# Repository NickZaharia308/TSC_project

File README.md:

# Nicusor-Alexandru Zaharia 335CA – Open-Source E-Book Reader

## Description
**OpenBook** is a fully open-source, ESP32-C6-powered e-book reader designed to be affordable, customizable, and easy to manufacture. It features a crisp e-paper display, modular hardware, and full documentation – empowering developers and hardware enthusiasts to build their own e-reader from scratch.

The project contains the **Product Design** with a complete [`schematic`](Hardware/Schematic.sch), [`PCB`](Hardware/PCB_2D.brd) and [`3D Model`](Mechanical/Completed%203D%20model%20v1.f3z).

---

## Repository Hierarchy

- Hardware
  ├── Schematic file (.sch)  
  └── Board layout file (.brd)  

- Manufacturing
  ├── Gerber files archive (gerbers.zip)  
  ├── Bill of Materials file (.bom)  
  └── Pick and Place file (.cpl)  

- Mechanical
  ├── 3D model of the complete device (PCB + battery + display + case) – exploded view (.step)  
  └── Fusion 360 project file of the complete device  

- Images
  └── Renders of the device

- LICENSE  
- README.md  

---

##  E-Book Reader Block Diagram

---

##   Design Process

1.  **Schematic Design:** The schematic was meticulously designed to align with the project's specified requirements. It highlights the important `components and modules`.
    
2.  **PCB Redesign:** The PCB layout was generated based on the size of the enclosure, and `components were strategically placed` according to design guidelines and best practices.
    
3.  **Routing Implementation:** Routing was used on both the top and bottom layers of the PCB. `Signal traces` were set to a width of 0.15mm while `the power traces` were organized into a dedicated net class named `Power class` routed with a width of 0.3mm to ensure optimal power distribution.
    
4.  **Ground Plane and Via Stitching:** `Ground planes` were implemented on both the top and bottom layers. `Via stitching` was applied, particularly in proximity to the ESP module, to establish effective interlayer connections and minimize ground impedance. `Vias` were used to interconnect the ground planes.
    
5.  **3D Model Integration:** `3D models` of the components were found with the link to them at the bottom of the README, integrated into Fusion 360, and accurately placed on the `PCB layout` to facilitate mechanical design and visualization.
    
6.  **Enclosure Integration:** The PCB was integrated into its intended enclosure. The enclosure design was adapted to accommodate buttons, connectors, and other external interface elements. `Battery` and `display` 3D models were developed positioned within the enclosure to ensure proper fit and alignment.

7.  **Export and Manufacturing Preparation:** The final stage involved `generating all necessary manufacturing` documentation, including Gerber files, Pick and Place (CPL) data, and the Bill of Materials (BOM), to prepare the design for fabrication and assembly.

---

## Decision Making

I switched the original [battery](https://www.tme.eu/Document/e0683d8c34e6d878124489f71bffb6ee/cel0014.pdf) from cellevia batteries with a similar [one](https://www.elektronik.ropla.eu/pdf/stock/aky/aky0099.pdf) (same electrical parameters) from akyga with a size that enters well in the enclosure and beside that it also has a lifecycle of `500 charges` as opossed to only `300 charges`

---

## Component Description and Interaction

### Microcontroller

* **ESP32-C6-WROOM-1-NI (U2):** This is the core of the board, a powerful microcontroller with Wi-Fi and Bluetooth Low Energy (BLE) connectivity. It is responsible for controlling all other components, processing data, and external communication.

### Power Supply

* **Li-Po Battery Charging Controller (MCP73831):** This circuit enables the board to be powered from a Li-Po battery and manages the charging process when an external power source is connected via the USB-C connector.
* **USB C connector:** Provides the interface for powering the board and potentially for data transfer. Includes `ESD (Electrostatic Discharge) protection`.
* **LDO Voltage Regulator (XC8220A331MR-G):** An LDO (Low Dropout) voltage regulator is used to provide a `stable 3.3V voltage` required for powering most of the components on the board, derived from the battery voltage or USB.
* **Supercapacitor (CPH3225A):** A supercapacitor is present, possibly to provide a backup power source for certain critical functions, such as the RTC module, in case the main power supply is interrupted.
* **Reverse Polarity Protection (MBR0530):** Schottky diodes are used to protect the circuits against incorrect polarity connection of the power source.
* **Capacitors (electrolytic, tantalum, ceramic):** Various types and values of capacitors are used for `power supply filtering, decoupling, and temporary energy storage` at different points in the circuit.

### Display

* **E-Paper Display Header (FH34SR-24S-0.5SH):** A header connector is provided for connecting an `E-Paper display`. This type of display is known for its low power consumption and image retention without power.
* **Display Type Selector:** A set of pull-up/pull-down resistors connected to ESP32-C6 pins allows for the detection of the connected E-Paper display type.

### Sensors

* **Environmental Sensor BME688:** This sensor integrates `temperature, humidity, atmospheric pressure, and air quality` (VOC - volatile organic compounds) measurement functions. It communicates with the ESP32-C6 via the `I2C` interface.
* **RTC Module DS3231SN:** A Real-Time Clock (RTC) module that maintains accurate time and date information, even when the board is powered off, being powered by the supercapacitor or a small battery. It communicates with the ESP32-C6 via `the I2C interface`.
* **Battery Charge Level (MAX17048G+T10):** A dedicated integrated circuit for monitoring the charge level of the Li-Po battery. It communicates with the ESP32-C6 via the `I2C interface`.

### User Interaction

* **Boot/IO Button (BOOT BUTTON):** A button used to force the ESP32-C6 into bootloader mode for programming or to perform an application-specific function.
* **Reset Button (RESET BUTTON):** A button to reset the ESP32-C6 microcontroller.
* **Change Button (CHANGE):** A button with an application-defined functionality, for navigation or selection.
* **CHG LED:** An LED indicator for the battery charging status.

### External Memory

* **External NOR Flash 64MB (W25Q512JVEIQ):** An external `64MB SPI flash memory`, used for storing firmware, data, or additional resources required by the application, exceeding the ESP32-C6's internal flash memory capacity. Good to keep `more books to read`.

### Connectivity and Interfaces

* **USB C connector:** For power and potential data transfer.
* **E-Paper Display Header:** Dedicated connector for the E-Paper display.
* **Qwiic/Stemma QT Connector:** A standard `I2C connector that allows for easy connection of additional I2C-compatible sensors or actuators`.
* **SPI ESD Protection Lines:** ESD protection circuits for the SPI communication lines, used for the external flash memory interface.
* **Test Pads (TP1-TP17):** Test points distributed across the board to facilitate debugging and `signal verification`.

### Miscellaneous

* **GND:** Multiple ground points for ensuring a stable voltage reference.
* **Resistors:** Various resistors are used for `pull-up, pull-down, current limiting, and voltage division`.
* **Diodes:** Diodes with various purposes, such as `protection or rectification`.
* **Inductor:** An inductor, part of the `power supply circuit or for EMI filtering`.
* **MOSFETs:** MOSFET transistors used for power switching or other control functions.

##   ESP32-C6 Pin Usage

The following list details the ESP32-C6 pins used and the reason for their use:

* **Pin 10 (3V3):** Power supply pin for the ESP32-C6, connected to the 3.3V rail generated by the LDO.
* **Pin 8 (GHD):** A ground (GND) pin.
* **Pin 5 (GHD):** A ground (GND) pin.
* **Pin 20 (EN):** Enable pin for the ESP32-C6, controlled by a power management circuit or connected to a pull-up to keep it active.
* **Pin 21 (1011):** Connected to the BOOT button. It is configured as an input and used to initiate the ESP32-C6's bootloader mode at startup or reset. A pull-up resistor (R BOOT 10K) ensures a default high logic level, and pressing the button connects it to GND.
* **Pin 22 (1013):** Connected to the RESET button. Similar to the BOOT button, it's an input used to reset the microcontroller.
* **Pin 23 (1013):** Connected to the CHANGE button. It is configured as an input and used to detect user action. A pull-up resistor (10K) ensures a default high logic level, and pressing the button connects it to GND.
* **Pin 19 (102):** Connected to the SDA (Serial Data) line of the I2C bus. This line is used for bidirectional data communication with the BME688 sensor, the DS3231SN RTC module, and the MAX17048G battery monitoring circuit. Pull-up resistors will be present on the I2C bus.
* **Pin 18 (1015):** Connected to the SCL (Serial Clock) line of the I2C bus. This line provides the synchronization clock signal for I2C communication with the peripherals mentioned above. Similar to SDA, it requires pull-up resistors.
* **Pin 17 (132):** Connected to the CE (Chip Enable) pin of the external flash memory W25Q512JVEIQ. This pin is used to select the flash memory chip for SPI communication.
* **Pin 16 (10220):** Connected to the HOLD/RESET pin of the external flash memory. This pin has multiple functions related to controlling the write and read operations of the flash memory.
* **Pin 15 (10):** Connected to the WP (Write Protect) pin of the external flash memory. This pin is used to protect certain sectors of the flash memory against accidental writing.
* **Pin 14 (CE BAT):** Connected to the CE (Chip Enable) pin of the MAX17048G battery monitoring circuit. Used to enable communication with this circuit on the I2C bus.

**Pins Connected to E-Paper Display Header (FH34SR-24S-0.5SH):**

Several ESP32-C6 pins will be connected to the E-Paper display header to control and transmit data to it.

* Powering the display (via "EPD Power").
* Transmitting the data and control signals necessary for updating the image on the display. This could include pins for an SPI interface (data, clock, chip select) or another interface specific to the E-Paper display controller.

**Pins Connected to BME688 Sensor:**

* **SDA (connected to Pin 19 of ESP32-C6):** I2C data line.
* **SCL (connected to Pin 18 of ESP32-C6):** I2C clock line.
* **VDDIO:** Power supply pin for the sensor's logic interface, connected to 3.3V.
* **VDD:** Power supply pin for the sensor, connected to 3.3V.
* **CSH:** Chip Select pin for the SPI interface.
* **SCK:** Serial Clock pin for the SPI interface.
* **SDO:** Serial Data Out pin for the SPI interface.

**Pins Connected to DS3231SN RTC Module:**

* **SDA (connected to Pin 19 of ESP32-C6):** I2C data line.
* **SCL (connected to Pin 18 of ESP32-C6):** I2C clock line.
* **VCC:** Power supply pin, connected to 3.3V or the supercapacitor voltage to maintain RTC operation.
* **SQW/INT# (ALERT):** An output pin that can be configured as a square wave output or an alarm/interrupt output, connected to a GPIO pin of the ESP32-C6.

**Pins Connected to MAX17048G Battery Charge Level Circuit:**

* **SDA (connected to Pin 19 of ESP32-C6):** I2C data line.
* **SCL (connected to Pin 18 of ESP32-C6):** I2C clock line.
* **CE (connected to Pin 14 of ESP32-C6):** Chip Enable pin for selecting the I2C circuit.
* **ALERT:** An alert output pin that can indicate low battery level or other events, connected to a GPIO pin of the ESP32-C6.

**Pins Connected to W25Q512JVEIQ (U1) External Flash Memory:**

* **CS# (Chip Select):** Connected to Pin 17 of ESP32-C6.
* **CLK (Serial Clock):** An ESP32-C6 SPI CLK pin.
* **MOSI (Master Out Slave In):** An ESP32-C6 SPI MOSI pin.
* **MISO (Master In Slave Out):** An ESP32-C6 SPI MISO pin.
* **HOLD/RESET#:** Connected to Pin 16 of ESP32-C6.
* **WP# (Write Protect):** Connected to Pin 15 of ESP32-C6.

**Pins Connected to Qwiic/Stemma QT Connector:**

* **SDA:** Connected to Pin 19 of ESP32-C6.
* **SCL:** Connected to Pin 18 of ESP32-C6.
* **VCC (3V3):** Power supply for connected devices.
* **GND:** Ground.

---

## Images

---

## Bill of Materials

| Component                                        | Product Link                | Datasheet                        |
|--------------------------------------------------|-----------------------------------|-----------------------------------|
| ESP32-C6 WROOM-1-N8                              | [SnapMagic](https://www.snapeda.com/parts/ESP32-C6-WROOM-1-N8/Espressif+Systems/view-part/?ref=eda)         | [Datasheet](https://www.snapeda.com/parts/ESP32-C6-WROOM-1-N8/Espressif%20Systems/datasheet/)     |
| ESP32C6 Varistor 1812                            | [Mouser](https://ro.mouser.com/ProductDetail/EPCOS-TDK/B72520T0350K062?qs=dEfas%2FXlABIszF52uu7vrg%3D%3D)        | [Datasheet](https://www.tdk-electronics.tdk.com/inf/75/db/CTVS_14/Surge_protection_series.pdf)     |
| ESP32 WROVER 0805 Capacitor                      | [Mouser](https://ro.mouser.com/ProductDetail/KYOCERA-AVX/SD0805S020S1R0?qs=jCA%252BPfw4LHbpkAoSnwrdjw%3D%3D)         | [Datasheet](https://ro.mouser.com/datasheet/2/40/schottky-3165252.pdf)     |
| ESP32 WROVER BME680 Sensor                       | [SnapMagic](https://www.snapeda.com/parts/BME680/Bosch/view-part/?welcome=home)        | [Datasheet](https://www.snapeda.com/parts/BME680/Bosch%20Sensortec/datasheet/)     |
| ESP32 WROVER MCP73831 Power Management           | [Mouser](https://eu.mouser.com/ProductDetail/Microchip-Technology/MCP73831T-2ACI-OT?qs=yUQqVecv4qvbBQBGbHx0Mw%3D%3D)         | [Datasheet](https://eu.mouser.com/datasheet/2/268/MCP73831_Family_Data_Sheet_DS20001984H-3441711.pdf)     || ESP32 WROVER P-Channel MOSFET                    | [Component Search Engine](https://componentsearchengine.com/part-view/DMG2305UX-7/Diodes%20Incorporated)         | [Datasheet](https://www.diodes.com//assets/Datasheets/DMG2305UX.pdf)     |
| LED Chip 0603                                    | [SnapMagic](https://www.snapeda.com/parts/KP-1608SURCK/Kingbright/view-part/?ref=search&t=LED%200603)        | [Datasheet](https://www.snapeda.com/parts/KP-1608SURCK/Kingbright/datasheet/)     |
| SJ                                               | [GrabCad](https://grabcad.com/library/solder-jumpers-1)         | [Datasheet](https://en.wikipedia.org/wiki/HTTP_404)     |
| LTSPICE Resistor 0402                            | [Component Search Engine](https://componentsearchengine.com/part-view/R0402%201%25%20100%20K%20(RC0402FR-07100KL)/YAGEO)        | [Datasheet](https://www.yageo.com/upload/media/product/products/datasheet/rchip/PYu-RC_Group_51_RoHS_L_12.pdf)     |
| RCL CPOL 3528                                    | [SnapMagic](https://www.snapeda.com/parts/TAJB475K025RNJ/AVX/view-part/?ref=dk&t=capacitor%203528&con_ref=None)        | [Datasheet](https://s3.amazonaws.com/snapeda/datasheet/TAJB475K025RNJ_AVX.pdf)     |
| 112A-TAAR-R03                                    | [Comet](https://store.comet.srl.ro/Catalogue/Product/43497/)         | [Datasheet](https://store.comet.bg/download-file.php?id=27596)     |
| Capacitor 0402                                   | [Component Search Engine](https://componentsearchengine.com/part-view/CC0402MRX5R5BB106/YAGEO)         | [Datasheet](https://componentsearchengine.com/Datasheets/2/CC0402MRX5R5BB106.pdf)     |
| 744043680 IND                                    | [Mouser](https://eu.mouser.com/ProductDetail/Wurth-Elektronik/744043680?qs=PGXP4M47uW6VkZq%252BkzjrHA%3D%3D)        | [Datasheet](https://www.we-online.com/components/products/datasheet/744043680.pdf)     |
| BD5229G-TR                                       | [Component Search Engine](https://componentsearchengine.com/part-view/BD5229G-TR/ROHM%20Semiconductor)         | [Datasheet](https://datasheet.datasheetarchive.com/originals/distributors/Datasheets_SAMA/f2b9741ef86007909f138d561a359946.pdf)     |
| Custom Button                                    | [Panasonic](https://industry.panasonic.com/global/en/products/control/switch/light-touch/number/evqpuj02k)        | [Datasheet](https://industry.panasonic.com/global/en/downloads?tab=catalog&small_g_cd=203&part_no=EVQPUJ02K&q=RVZRUFVKMDJLJTdDMTMlN0MyMDMlN0MzNDU5JTdDMSU3QyU3QzIlN0M%3D)     |
| CPH3225A                                         | [SnapMagic](https://www.snapeda.com/parts/CPH3225A/Seiko+Instruments/view-part/?ref=eda)         | [Datasheet](https://www.snapeda.com/parts/CPH3225A/Seiko%20Instruments/datasheet/)     |
| DS3231SN RTC                                     | [SnapMagic](https://www.snapeda.com/parts/DS3231SN%23/Analog+Devices/view-part/?ref=eda)        | [Datasheet](https://www.snapeda.com/parts/DS3231SN%23/Analog%20Devices/datasheet/)     |
| FH34SRJ-24S-0.5SH Connector                      | [Component Search Engine](https://componentsearchengine.com/part-view/FH34SRJ-24S-0.5SH(99)/Hirose)        | [Datasheet](https://www.hirose.com/en/product/document?clcode=CL0580-1255-6-99&productname=FH34SRJ-24S-0.5SH(99)&series=FH34SRJ&documenttype=2DDrawing&lang=en&documentid=0000990903)     |
| MAX17048G+T10 Battery Fuel Gauge                 | [SnapMagic](https://www.snapeda.com/parts/MAX17048G+T10/Analog+Devices/view-part/?ref=eda)         | [Datasheet](https://www.snapeda.com/parts/MAX17048G+T10/Analog%20Devices/datasheet/)     |
| MBR0530 Schottky Diode                           | [SnapMagic](https://www.snapeda.com/parts/MBR0530/Onsemi/view-part/?ref=eda)        | [Datasheet](https://www.snapeda.com/parts/MBR0530/ON%20Semiconductor/datasheet/)     |
| PGB1010603MR Inductor                            | [SnapMagic](https://www.snapeda.com/parts/PGB1010603MR/Littelfuse/view-part/?ref=eda)         | [Datasheet](https://www.snapeda.com/parts/PGB1010603MR/Littelfuse%20Inc./datasheet/)     |
| QWIIC Connector                                  | [Mouser](https://eu.mouser.com/ProductDetail/Adafruit/4208?qs=PzGy0jfpSMtbScLbr0L5dw%3D%3D)        | [Datasheet](https://en.wikipedia.org/wiki/HTTP_404)     |
| USB4110-GF-A USB Hub                             | [Component Search Engine](https://componentsearchengine.com/part-view/USB4110-GF-A/GCT%20(GLOBAL%20CONNECTOR%20TECHNOLOGY))         | [Datasheet](https://gct.co/files/drawings/usb4110.pdf)     |
| SI1308EDL-T1-GE3 MOSFET                          | [SnapMagic](https://www.snapeda.com/parts/SI1308EDL-T1-GE3/Vishay+Siliconix/view-part/?ref=eda)        | [Datasheet](https://en.wikipedia.org/wiki/HTTP_404)     |
| TPTP20R                                          | [Comet](https://easyeda.com/component/7524403feb2642ac9f9f26dfb93ceacf)         | [Datasheet](https://easyeda.com/component/7524403feb2642ac9f9f26dfb93ceacf)     |
| USBLC6-2SC6Y USB Surge Protection                | [SnapMagic](https://www.snapeda.com/parts/USBLC6-2SC6Y/STMicroelectronics/view-part/?ref=eda)        | [Datasheet](https://www.snapeda.com/parts/USBLC6-2SC6Y/STMicroelectronics/datasheet/)     |
| W25Q512JVEIQ Flash Memory                        | [SnapMagic](https://www.snapeda.com/parts/W25Q512JVEIQ/Winbond+Electronics/view-part/?ref=eda)         | [Datasheet](https://www.snapeda.com/parts/W25Q512JVEIQ/Winbond%20Electronics/datasheet/)     |
| XC6220A331MR-G Voltage Regulator                 | [Component Search Engine](https://componentsearchengine.com/part-view/XC6220A331MR-G/Torex)        | [Datasheet](https://product.torexsemi.com/system/files/series/xc6220.pdf)     |

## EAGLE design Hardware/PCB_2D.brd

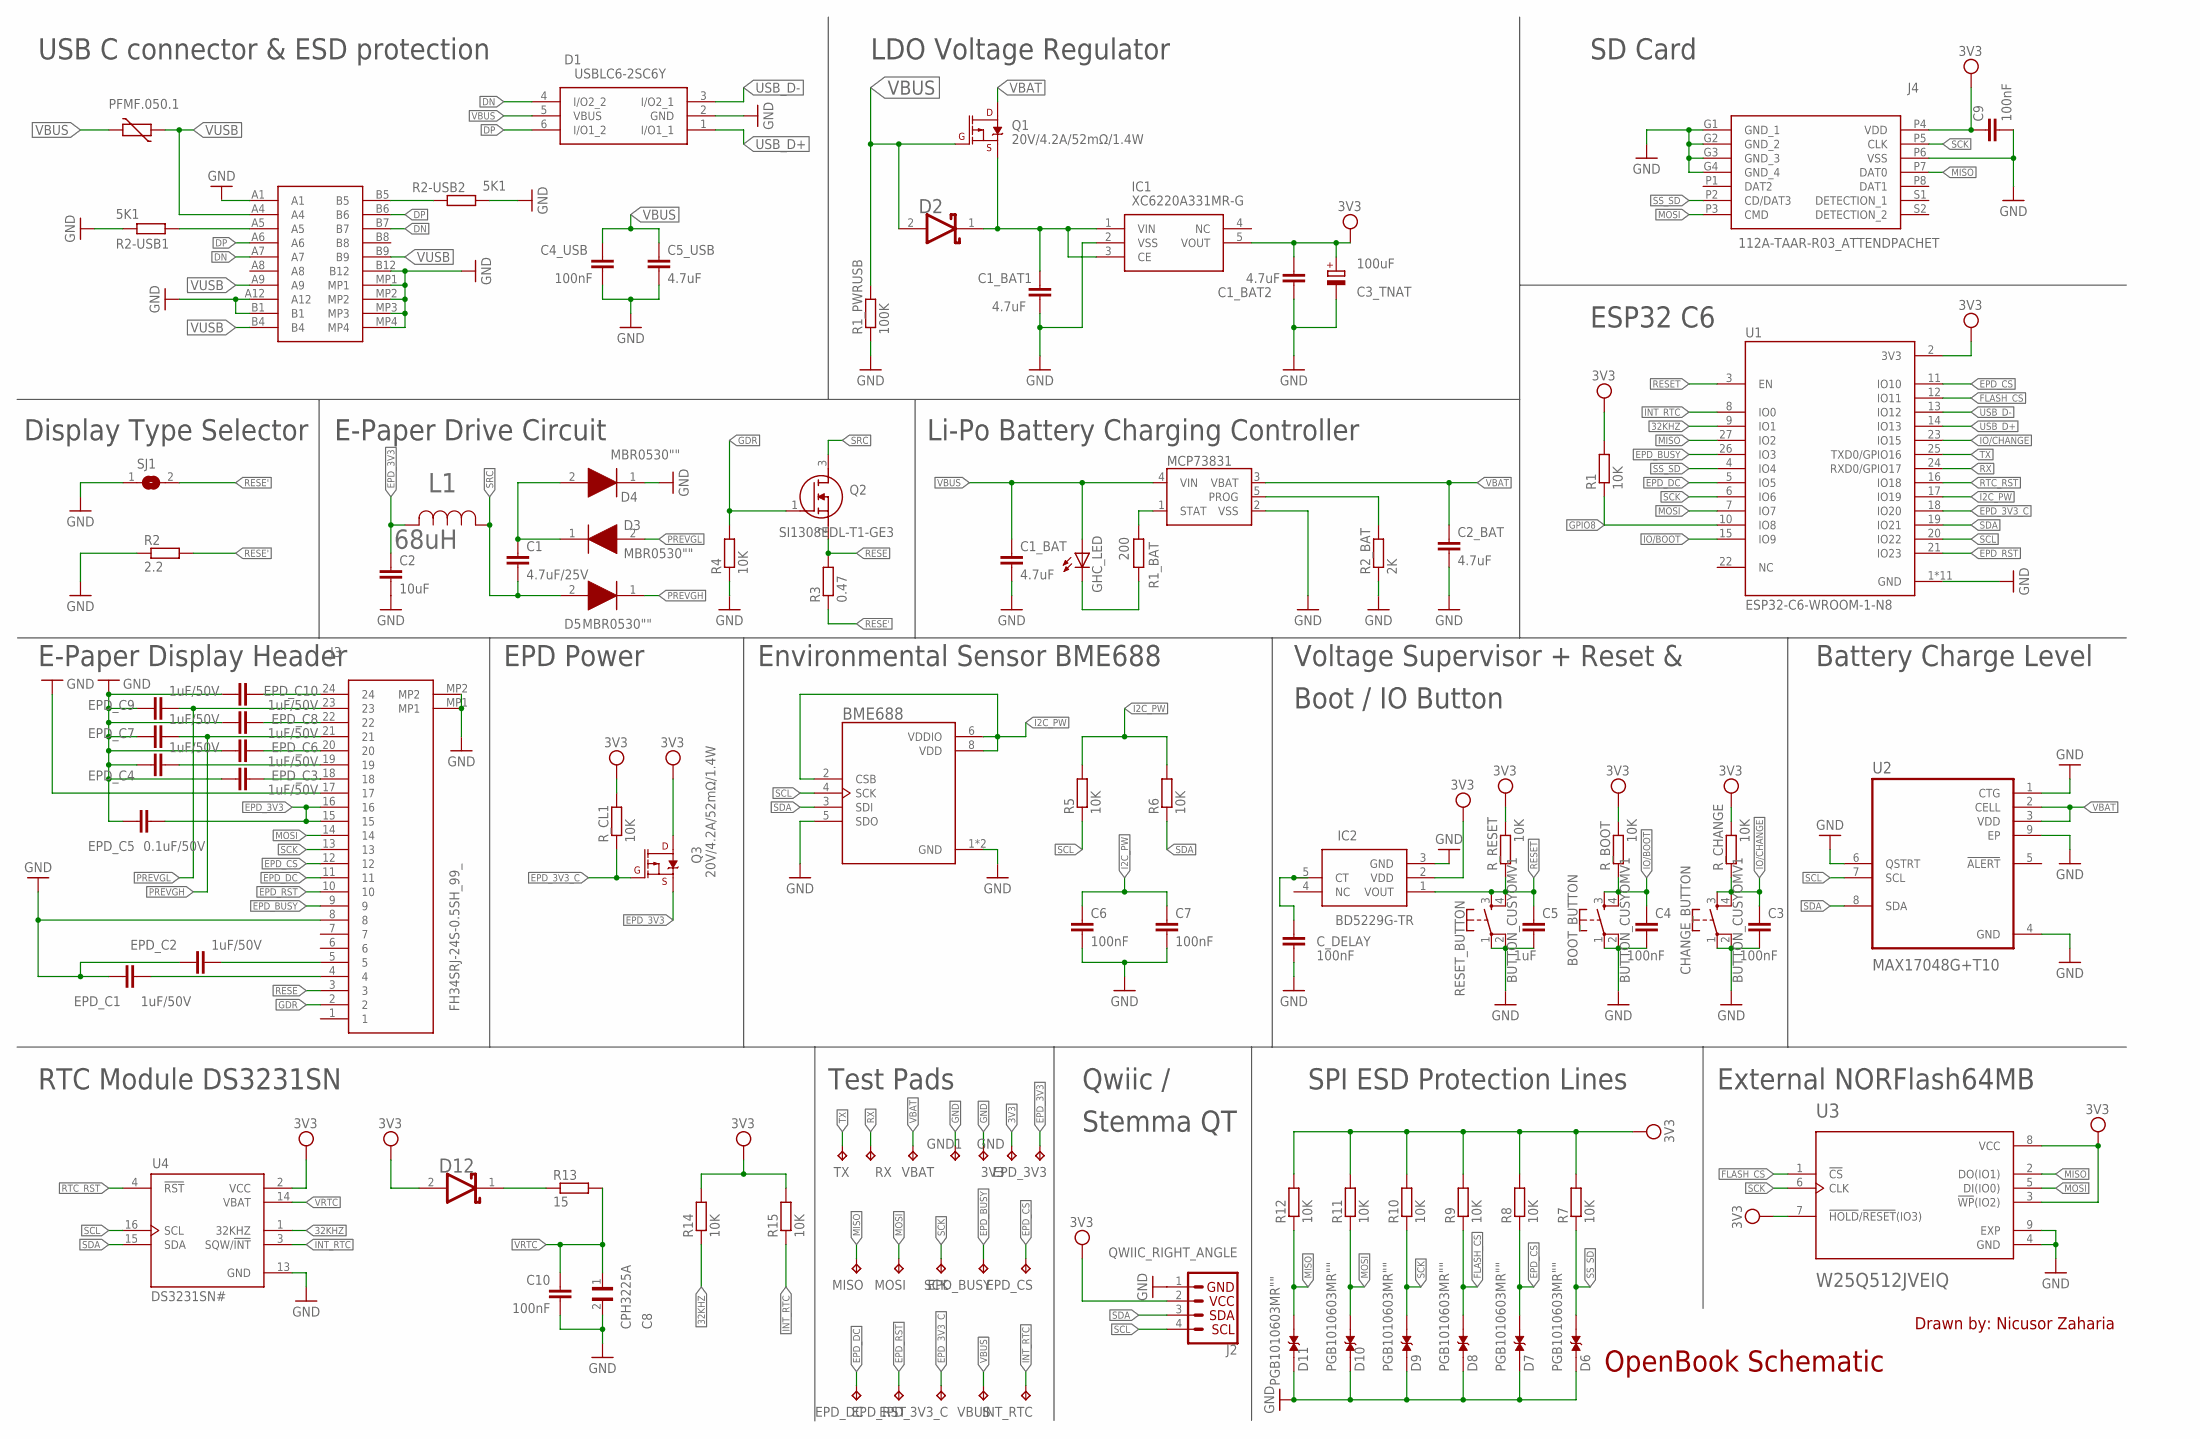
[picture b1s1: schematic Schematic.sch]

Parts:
3V3: TPTP20R; TP20R
BME688: ESP32_WROVER_BME680_BME680; ESP32_WROVER_BME680_PSON80P300X300X100-8N
BOOT_BUTTON: BUTTON_CUSYOMV1; MYBUTTON
C1: 4.7uF/25V; EAGLE-LTSPICE_C0402
C1_BAT, C1_BAT1, C1_BAT2, C2_BAT, C5_USB: 4.7uF; EAGLE-LTSPICE_C0402
C2: 10uF; EAGLE-LTSPICE_C0402
C3, C4, C4_USB, C6, C7, C9, C10: 100nF; EAGLE-LTSPICE_C0402
C3_TNAT: 100uF; RCL_CT3528
C5: 1uF; EAGLE-LTSPICE_C0402
C8: CPH3225A; CAPCP3225X100N
CHANGE_BUTTON: BUTTON_CUSYOMV1; MYBUTTON
C_DELAY: 100nF; EAGLE-LTSPICE_C0402
D1: USBLC6-2SC6Y; SOT95P280X145-6N
D2, D12: ESP32_WROVER_AVX---SD0805S020S1R0_AVX_SD0805S020S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; ESP32_WROVER_AVX---SD0805S020S1R0_AVX_SD0805S020S1R0_0
D3, D4, D5: MBR0530""; SOD3716X135N
D6, D7, D8, D9, D10, D11: PGB1010603MR""; DIOC1608X36N
EPD_3V3, EPD_3V3_C: TPTP20R; TP20R
EPD_BUSY: TPTP20R; TP20R
EPD_C1, EPD_C2, EPD_C3, EPD_C4, EPD_C6, EPD_C7, EPD_C8, EPD_C9, EPD_C10: 1uF/50V; EAGLE-LTSPICE_C0402
EPD_C5: 0.1uF/50V; EAGLE-LTSPICE_C0402
EPD_CS: TPTP20R; TP20R
EPD_DC: TPTP20R; TP20R
EPD_RST: TPTP20R; TP20R
GHC_LED: ADAFRUIT_LEDCHIP-LED0603; ADAFRUIT_CHIP-LED0603
GND, GND1: TPTP20R; TP20R
IC1: XC6220A331MR-G; SOT95P280X120-5N
IC2: BD5229G-TR; SOT95P280X125-5N
INT_RTC: TPTP20R; TP20R
J1: SAMACSYS_PARTS_USB4110-GF-A; SAMACSYS_PARTS_USB4110GFA
J2: QWIIC_RIGHT_ANGLE; JST04_1MM_RA
J3: FH34SRJ-24S-0.5SH_99_; FH34SRJ24S05SH99
J4: 112A-TAAR-R03_ATTENDPACHET; 112ATAARR03ATTEND
L1: 68uH; IND_4828-WE-TPC_WRE
MCP73831: ESP32_WROVER_SPARKFUN-IC-POWER_MCP73831; ESP32_WROVER_SPARKFUN-IC-POWER_SOT23-5
MISO: TPTP20R; TP20R
MOSI: TPTP20R; TP20R
PFMF.050.1: ESP32C6_VARISTORCN1812; ESP32C6_VARISTOR_CT/CN1812
Q1, Q3: 20V/4.2A/52mΩ/1.4W; ESP32_WROVER_SPARKFUN-DISCRETESEMI_SOT23-3
Q2: SI1308EDL-T1-GE3; SOT65P210X110-3N
R1, R4, R5, R6, R7, R8, R9, R10, R11, R12, R14, R15: 10K; ESP32_WROVER_EAGLE-LTSPICE_R0402
R1_BAT: 200; ESP32_WROVER_EAGLE-LTSPICE_R0402
R1_PWRUSB: 100K; ESP32_WROVER_EAGLE-LTSPICE_R0402
R2: 2.2; ESP32_WROVER_EAGLE-LTSPICE_R0402
R2-USB1, R2-USB2: 5K1; ESP32_WROVER_EAGLE-LTSPICE_R0402
R2_BAT: 2K; ESP32_WROVER_EAGLE-LTSPICE_R0402
R3: 0.47; ESP32_WROVER_EAGLE-LTSPICE_R0402
R13: 15; ESP32_WROVER_EAGLE-LTSPICE_R0402
RESET_BUTTON: BUTTON_CUSYOMV1; MYBUTTON
RX: TPTP20R; TP20R
R_BOOT: 10K; ESP32_WROVER_EAGLE-LTSPICE_R0402
R_CHANGE: 10K; ESP32_WROVER_EAGLE-LTSPICE_R0402
R_CL1: 10K; ESP32_WROVER_EAGLE-LTSPICE_R0402
R_RESET: 10K; ESP32_WROVER_EAGLE-LTSPICE_R0402
SCK: TPTP20R; TP20R
SJ1: SJ
TX: TPTP20R; TP20R
U1: ESP32-C6-WROOM-1-N8; XCVR_ESP32-C6-WROOM-1-N8
U2: MAX17048G+T10; SON50P200X200X80-9N
U3: W25Q512JVEIQ; SON127P600X800X80-9N
U4: DS3231SN#; SOIC127P1032X265-16N
VBAT: TPTP20R; TP20R
VBUS: TPTP20R; TP20R

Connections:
3V3: 3V3.TP, C1_BAT2.1, C3_TNAT.+, C9.1, D12.2 (ANODE), IC1.5 (VOUT), IC2.2 (VDD), J2.2, J4.P4 (VDD), Q3.3 (D), R1.2, R7.2, R8.2, R9.2, R10.2, R11.2, R12.2, R14.2, R15.2, R_BOOT.2, R_CHANGE.2, R_CL1.2, R_RESET.2, U1.2 (3V3), U3.3 (!WP!(IO2)), U3.7 (!HOLD!/!RESET!(IO3)), U3.8 (VCC), U4.2 (VCC)
32KHZ: R14.1, U1.9 (IO1), U4.1 (32KHZ)
DN: D1.4 (I/O2_2), J1.A7, J1.B7
DP: D1.6 (I/O1_2), J1.A6, J1.B6
EPD_3V3: C2.1, EPD_3V3.TP, EPD_C5.2, J3.15, J3.16, L1.2, Q3.2 (S)
EPD_3V3_C: EPD_3V3_C.TP, Q3.1 (G), R_CL1.1, U1.18 (IO20)
EPD_BUSY: EPD_BUSY.TP, J3.9, U1.26 (IO3)
EPD_CS: D7.2, EPD_CS.TP, J3.12, R8.1, U1.11 (IO10)
EPD_DC: EPD_DC.TP, J3.11, U1.5 (IO5)
EPD_RST: EPD_RST.TP, J3.10, U1.21 (IO23)
FLASH_CS: D8.2, R9.1, U1.12 (IO11), U3.1 (!CS)
GDR: J3.2, Q2.1 (G), R4.2
GND: BME688.1 (GND), BME688.5 (SDO), BME688.7 (GND), BOOT_BUTTON.1, BOOT_BUTTON.2, C1_BAT.2, C1_BAT1.2, C1_BAT2.2, C2.2, C2_BAT.2, C3.2, C3_TNAT.-, C4.2, C4_USB.2, C5.2, C5_USB.2, C6.2, C7.2, C8.2, C9.2, C10.2, CHANGE_BUTTON.1, CHANGE_BUTTON.2, C_DELAY.2, D1.2 (GND), D4.1 (K), D6.1, D7.1, D8.1, D9.1, D10.1, D11.1, EPD_C1.1, EPD_C2.1, EPD_C3.1, EPD_C4.1, EPD_C5.1, EPD_C6.1, EPD_C7.1, EPD_C8.1, EPD_C9.1, EPD_C10.1, GND.TP, GND1.TP, IC1.2 (VSS), IC2.3 (GND), J1.A1, J1.A12, J1.B1, J1.B12, J1.MP1, J1.MP2, J1.MP3, J1.MP4, J2.1, J3.8, J3.17, J3.MP1, J3.MP2, J4.G1 (GND_1), J4.G2 (GND_2), J4.G3 (GND_3), J4.G4 (GND_4), J4.P6 (VSS), MCP73831.2 (VSS), R1_PWRUSB.1, R2.1, R2-USB1.1, R2-USB2.2, R2_BAT.1, R4.1, RESET_BUTTON.1, RESET_BUTTON.2, SJ1.1, U1.1 (GND), U1.28 (GND), U1.29_1 (GND), U1.29_2 (GND), U1.29_3 (GND), U1.29_4 (GND), U1.29_5 (GND), U1.29_6 (GND), U1.29_7 (GND), U1.29_8 (GND), U1.29_9 (GND), U2.1 (CTG), U2.4 (GND), U2.6 (QSTRT), U2.9 (EP), U3.4 (GND), U3.9 (EXP), U4.13 (GND)
GPIO8: R1.1, U1.10 (IO8)
I2C_PW: BME688.2 (CSB), BME688.6 (VDDIO), BME688.8 (VDD), C6.1, C7.1, R5.2, R6.2, U1.17 (IO19)
INT_RTC: INT_RTC.TP, R15.1, U1.8 (IO0), U4.3 (SQW/!INT)
IO/BOOT: BOOT_BUTTON.3, BOOT_BUTTON.4, C4.1, R_BOOT.1, U1.15 (IO9)
IO/CHANGE: C3.1, CHANGE_BUTTON.3, CHANGE_BUTTON.4, R_CHANGE.1, U1.23 (IO15)
MISO: D11.2, J4.P7 (DAT0), MISO.TP, R12.1, U1.27 (IO2), U3.2 (DO(IO1))
MOSI: D10.2, J3.14, J4.P3 (CMD), MOSI.TP, R11.1, U1.7 (IO7), U3.5 (DI(IO0))
unnamed: J1.A5, R2-USB1.2
unnamed: J1.B5, R2-USB2.1
unnamed: C1_BAT1.1, D2.1 (CATHODE), IC1.1 (VIN), IC1.3 (CE), Q1.2 (S)
unnamed: MCP73831.1 (STAT), R1_BAT.2
unnamed: MCP73831.5 (PROG), R2_BAT.2
unnamed: GHC_LED.C, R1_BAT.1
unnamed: C_DELAY.1, IC2.5 (CT)
unnamed: EPD_C3.2, J3.18
unnamed: C1.1, D3.1 (K), D4.2 (A)
unnamed: EPD_C6.2, J3.20
unnamed: EPD_C1.2, J3.4
unnamed: D12.1 (CATHODE), R13.1
unnamed: EPD_C2.2, J3.5
unnamed: EPD_C8.2, J3.22
unnamed: EPD_C10.2, J3.24
unnamed: EPD_C4.2, J3.19
PREVGH: D5.1 (K), EPD_C7.2, J3.21
PREVGL: D3.2 (A), EPD_C9.2, J3.23
RESE: J3.3, Q2.2 (S), R3.2
RESE': R2.2, R3.1, SJ1.2
RESET: C5.1, IC2.1 (VOUT), RESET_BUTTON.3, RESET_BUTTON.4, R_RESET.1, U1.3 (EN)
RTC_RST: U1.16 (IO18), U4.4 (!RST)
RX: RX.TP, U1.24 (RXD0/GPIO17)
SCK: D9.2, J3.13, J4.P5 (CLK), R10.1, SCK.TP, U1.6 (IO6), U3.6 (CLK)
SCL: BME688.4 (SCK), J2.4, R5.1, U1.20 (IO22), U2.7 (SCL), U4.16 (SCL)
SDA: BME688.3 (SDI), J2.3, R6.1, U1.19 (IO21), U2.8 (SDA), U4.15 (SDA)
SRC: C1.2, D5.2 (A), L1.1, Q2.3 (D)
SS_SD: D6.2, J4.P2 (CD/DAT3), R7.1, U1.4 (IO4)
TX: TX.TP, U1.25 (TXD0/GPIO16)
USB_D+: D1.1 (I/O1_1), U1.14 (IO13)
USB_D-: D1.3 (I/O2_1), U1.13 (IO12)
VBAT: C2_BAT.1, MCP73831.3 (VBAT), Q1.3 (D), U2.2 (CELL), U2.3 (VDD), VBAT.TP
VBUS: C1_BAT.1, C4_USB.1, C5_USB.1, D1.5 (VBUS), D2.2 (ANODE), GHC_LED.A, MCP73831.4 (VIN), PFMF.050.1.2, Q1.1 (G), R1_PWRUSB.2, VBUS.TP
VRTC: C8.1, C10.1, R13.2, U4.14 (VBAT)
VUSB: J1.A4, J1.A9, J1.B4, J1.B9, PFMF.050.1.1

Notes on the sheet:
USB C connector & ESD protection
LDO Voltage Regulator
SD Card
ESP32 C6
Li-Po Battery Charging Controller
E-Paper Drive Circuit
Display Type Selector
Battery Charge Level
Voltage Supervisor + Reset &
Boot / IO Button
Environmental Sensor BME688
EPD Power
E-Paper Display Header
External NORFlash64MB
SPI ESD Protection Lines
Qwiic /
Stemma QT
Test Pads
RTC Module DS3231SN
Drawn by: Nicusor Zaharia
OpenBook Schematic

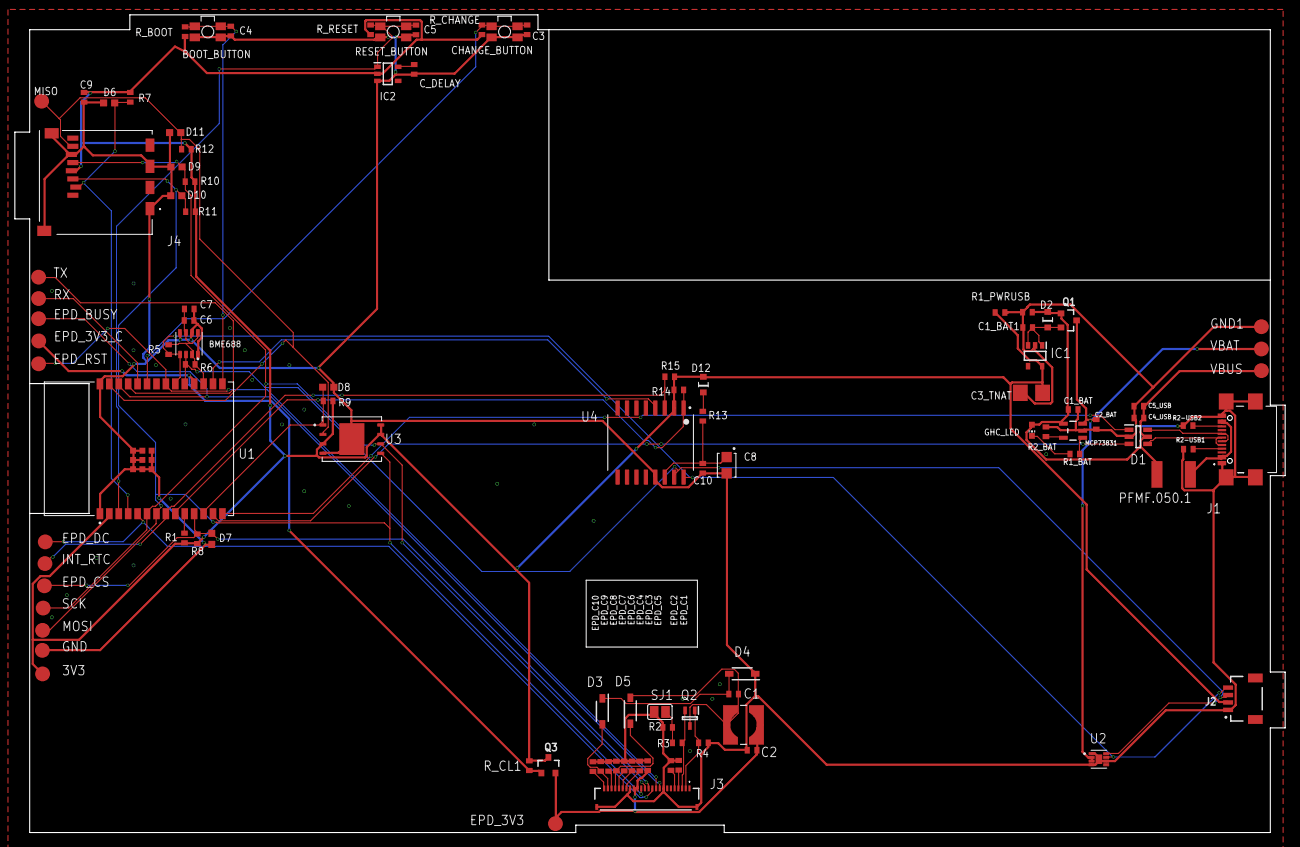
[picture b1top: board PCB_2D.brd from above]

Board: 2 copper layers, 171.2 x 110.2 mm, 103 parts (0 on the bottom side), 55 nets.

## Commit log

2025-04-06 Add Schematic and 2D PCB files
2025-04-06 Add manufacturing files
    Added gerbers, bill of materials and Pick and Place file
2025-04-06 Add mechanical files
    Complete models for the 3d model both exploded and embedded
2025-04-06 Add images
    Add .png images with final product
2025-04-06 Add README.md
2025-04-12 Fixes #1. #2. #3. #4. #5. #6. #7 #8 #9: Improved 3D models, silkscreen and schematic
2025-04-14 Create LICENSE
2025-04-14 Add the reviewed version for the mechanical files

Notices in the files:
parts and their libraries:
COPYRIGHT: Copyright (C) 2024 Ultra Librarian. All rights reserved.
